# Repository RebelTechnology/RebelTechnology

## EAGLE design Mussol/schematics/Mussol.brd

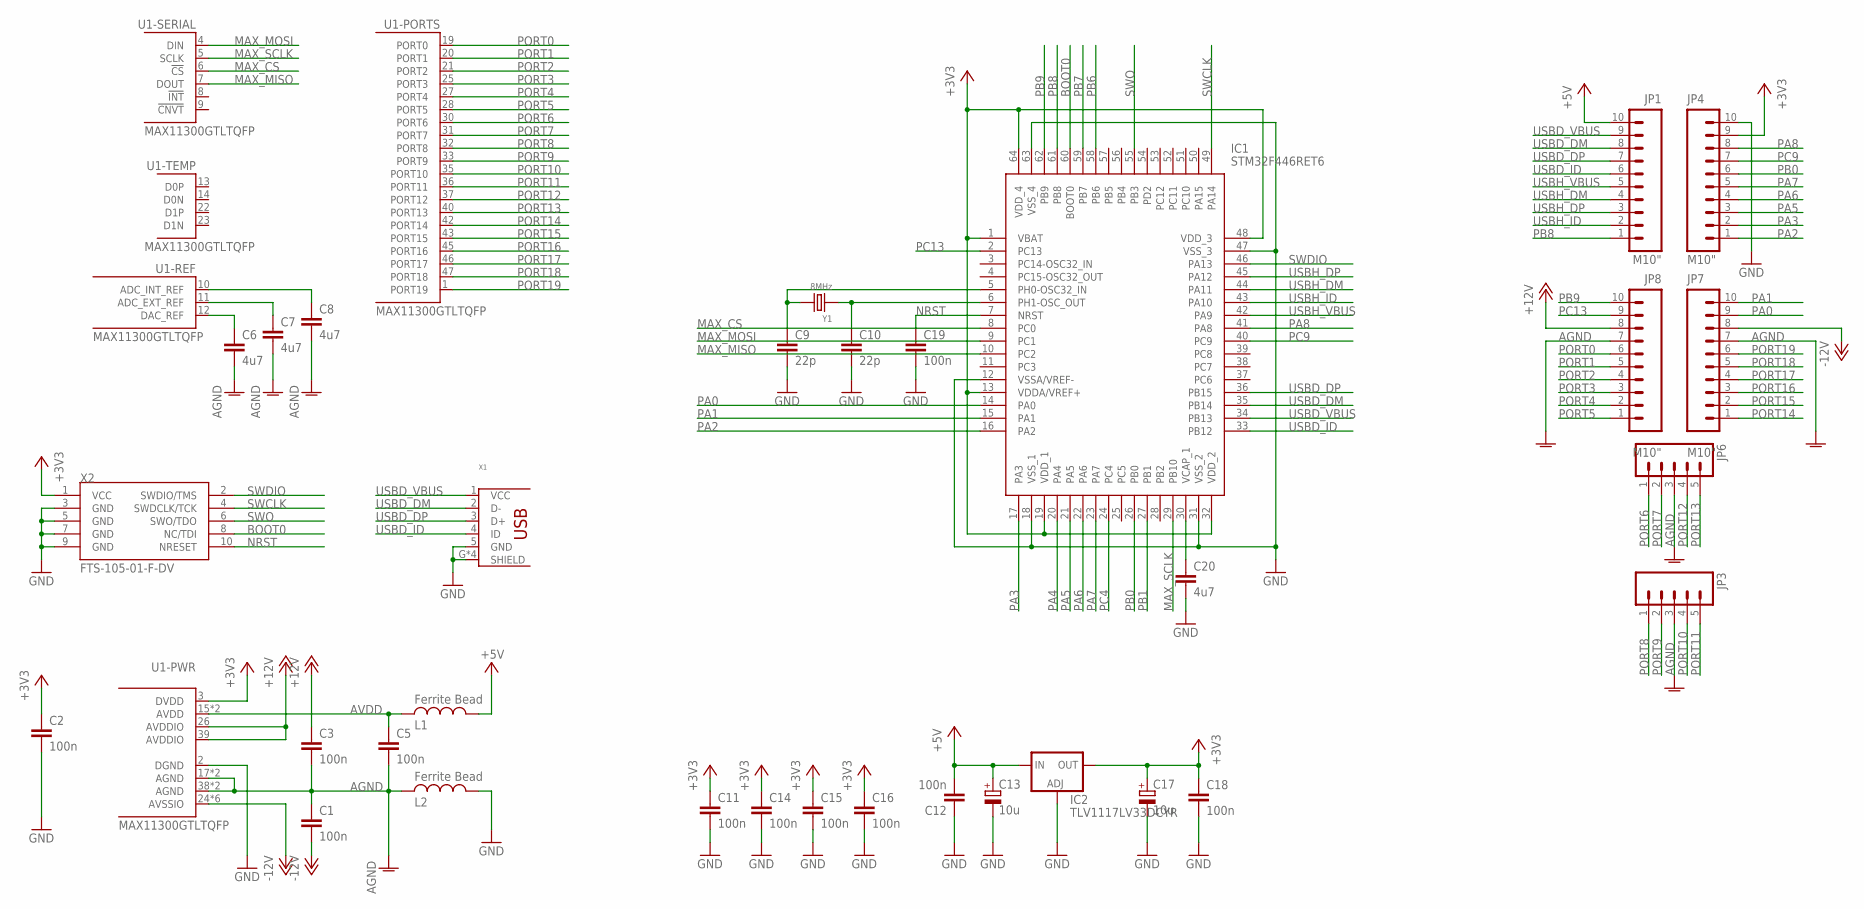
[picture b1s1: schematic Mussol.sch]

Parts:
C1, C2, C3, C5, C11, C12, C14, C15, C16, C18, C19: 100n; C0402
C6, C7, C8, C20: 4u7; C0603
C9, C10: 22p; C0402
C13, C17: 10u; UD-4X5,8_NICHICON
IC1: STM32F446RET6; QFP50P1200X1200X160-64N
IC2: TLV1117LV33DCYR; SOT223
JP1, JP4, JP7, JP8: M10"; 1X10
JP3, JP6: M05PTH; 1X05
L1, L2: Ferrite Bead; 0603
U1: MAX11300GTLTQFP; TQFP48
X1: USB_HRS_ZX62-B-5PA(11)MICRO.B; HRS_ZX62RD-AB-5P8
X2: FTS-105-01-F-DV; 2X5_1.27MM_SMD
Y1: 8MHz; X2-SMD-5.0X3.2X1.3MM

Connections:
+3V3: C2.1, C11.1, C14.1, C15.1, C16.1, C17.+, C18.1, IC1.1 (VBAT), IC1.13 (VDDA/VREF+), IC1.19 (VDD_1), IC1.32 (VDD_2), IC1.48 (VDD_3), IC1.64 (VDD_4), IC2.4 (OUT), JP4.9, U1.3 (DVDD), X2.1 (VCC)
+5V: C12.2, C13.+, IC2.3 (IN), JP1.10, L1.1
+12V: C3.1, JP8.8, U1.26 (AVDDIO), U1.39 (AVDDIO)
-12V: C1.2, JP7.8, U1.24 (AVSSIO), U1.29 (AVSSIO), U1.34 (AVSSIO), U1.41 (AVSSIO), U1.44 (AVSSIO), U1.48 (AVSSIO)
AGND: C1.1, C3.2, C5.2, C6.2, C7.2, C8.2, JP3.3, JP6.3, JP7.7, JP8.7, L2.2, U1.17 (AGND), U1.18 (AGND), U1.38 (AGND), U1.EP (AGND)
AVDD: C5.1, L1.2, U1.15 (AVDD), U1.16 (AVDD)
BOOT0: IC1.60 (BOOT0), X2.8 (NC/TDI)
GND: C2.2, C9.2, C10.2, C11.2, C12.1, C13.-, C14.2, C15.2, C16.2, C17.-, C18.2, C19.2, C20.2, IC1.12 (VSSA/VREF-), IC1.18 (VSS_1), IC1.31 (VSS_2), IC1.47 (VSS_3), IC1.63 (VSS_4), IC2.1 (ADJ), JP4.10, L2.1, U1.2 (DGND), X1.5 (GND), X1.G (SHIELD), X1.G2 (SHIELD), X1.G3 (SHIELD), X1.G4 (SHIELD), X2.3 (GND), X2.5 (GND), X2.7 (GND), X2.9 (GND)
MAX_CS: IC1.8 (PC0), U1.6 (!CS!)
MAX_MISO: IC1.10 (PC2), U1.7 (DOUT)
MAX_MOSI: IC1.9 (PC1), U1.4 (DIN)
MAX_SCLK: IC1.29 (PB10), U1.5 (SCLK)
unnamed: C8.1, U1.10 (ADC_INT_REF)
unnamed: C20.1, IC1.30 (VCAP_1)
unnamed: C7.1, U1.11 (ADC_EXT_REF)
unnamed: C6.1, U1.12 (DAC_REF)
unnamed: C10.1, IC1.6 (PH1-OSC_OUT), Y1.1
unnamed: C9.1, IC1.5 (PH0-OSC32_IN), Y1.2
NRST: C19.1, IC1.7 (NRST), X2.10 (NRESET)
PA0: IC1.14 (PA0), JP7.9
PA1: IC1.15 (PA1), JP7.10
PA2: IC1.16 (PA2), JP4.1
PA3: IC1.17 (PA3), JP4.2
PA4: IC1.20 (PA4)
PA5: IC1.21 (PA5), JP4.3
PA6: IC1.22 (PA6), JP4.4
PA7: IC1.23 (PA7), JP4.5
PA8: IC1.41 (PA8), JP4.8
PB0: IC1.26 (PB0), JP4.6
PB1: IC1.27 (PB1)
PB6: IC1.58 (PB6)
PB7: IC1.59 (PB7)
PB8: IC1.61 (PB8), JP1.1
PB9: IC1.62 (PB9), JP8.10
PC4: IC1.24 (PC4)
PC9: IC1.40 (PC9), JP4.7
PC13: IC1.2 (PC13), JP8.9
PORT0: JP8.6, U1.19 (PORT0)
PORT1: JP8.5, U1.20 (PORT1)
PORT2: JP8.4, U1.21 (PORT2)
PORT3: JP8.3, U1.25 (PORT3)
PORT4: JP8.2, U1.27 (PORT4)
PORT5: JP8.1, U1.28 (PORT5)
PORT6: JP6.1, U1.30 (PORT6)
PORT7: JP6.2, U1.31 (PORT7)
PORT8: JP3.1, U1.32 (PORT8)
PORT9: JP3.2, U1.33 (PORT9)
PORT10: JP3.4, U1.35 (PORT10)
PORT11: JP3.5, U1.36 (PORT11)
PORT12: JP6.4, U1.37 (PORT12)
PORT13: JP6.5, U1.40 (PORT13)
PORT14: JP7.1, U1.42 (PORT14)
PORT15: JP7.2, U1.43 (PORT15)
PORT16: JP7.3, U1.45 (PORT16)
PORT17: JP7.4, U1.46 (PORT17)
PORT18: JP7.5, U1.47 (PORT18)
PORT19: JP7.6, U1.1 (PORT19)
SWCLK: IC1.49 (PA14), X2.4 (SWDCLK/TCK)
SWDIO: IC1.46 (PA13), X2.2 (SWDIO/TMS)
SWO: IC1.55 (PB3), X2.6 (SWO/TDO)
USBD_DM: IC1.35 (PB14), JP1.8, X1.2 (D-)
USBD_DP: IC1.36 (PB15), JP1.7, X1.3 (D+)
USBD_ID: IC1.33 (PB12), JP1.6, X1.4 (ID)
USBD_VBUS: IC1.34 (PB13), JP1.9, X1.1 (VCC)
USBH_DM: IC1.44 (PA11), JP1.4
USBH_DP: IC1.45 (PA12), JP1.3
USBH_ID: IC1.43 (PA10), JP1.2
USBH_VBUS: IC1.42 (PA9), JP1.5

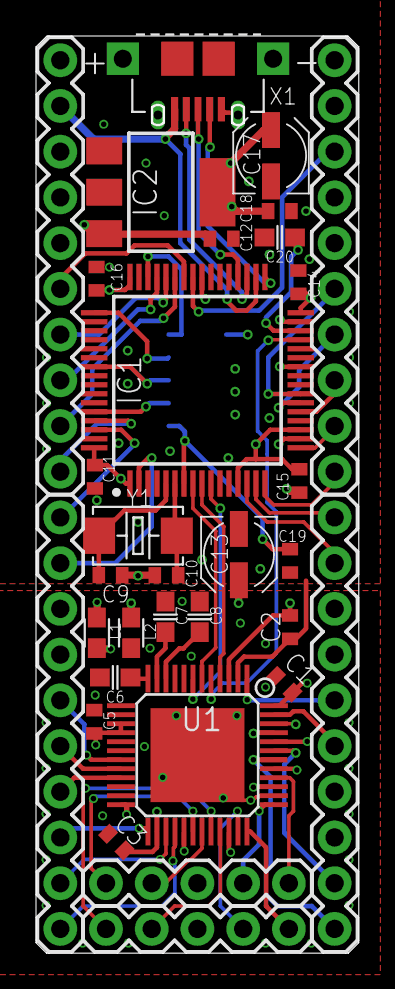
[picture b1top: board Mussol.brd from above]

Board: 4 copper layers, 17.9 x 51.0 mm, 33 parts (1 on the bottom side), 63 nets.

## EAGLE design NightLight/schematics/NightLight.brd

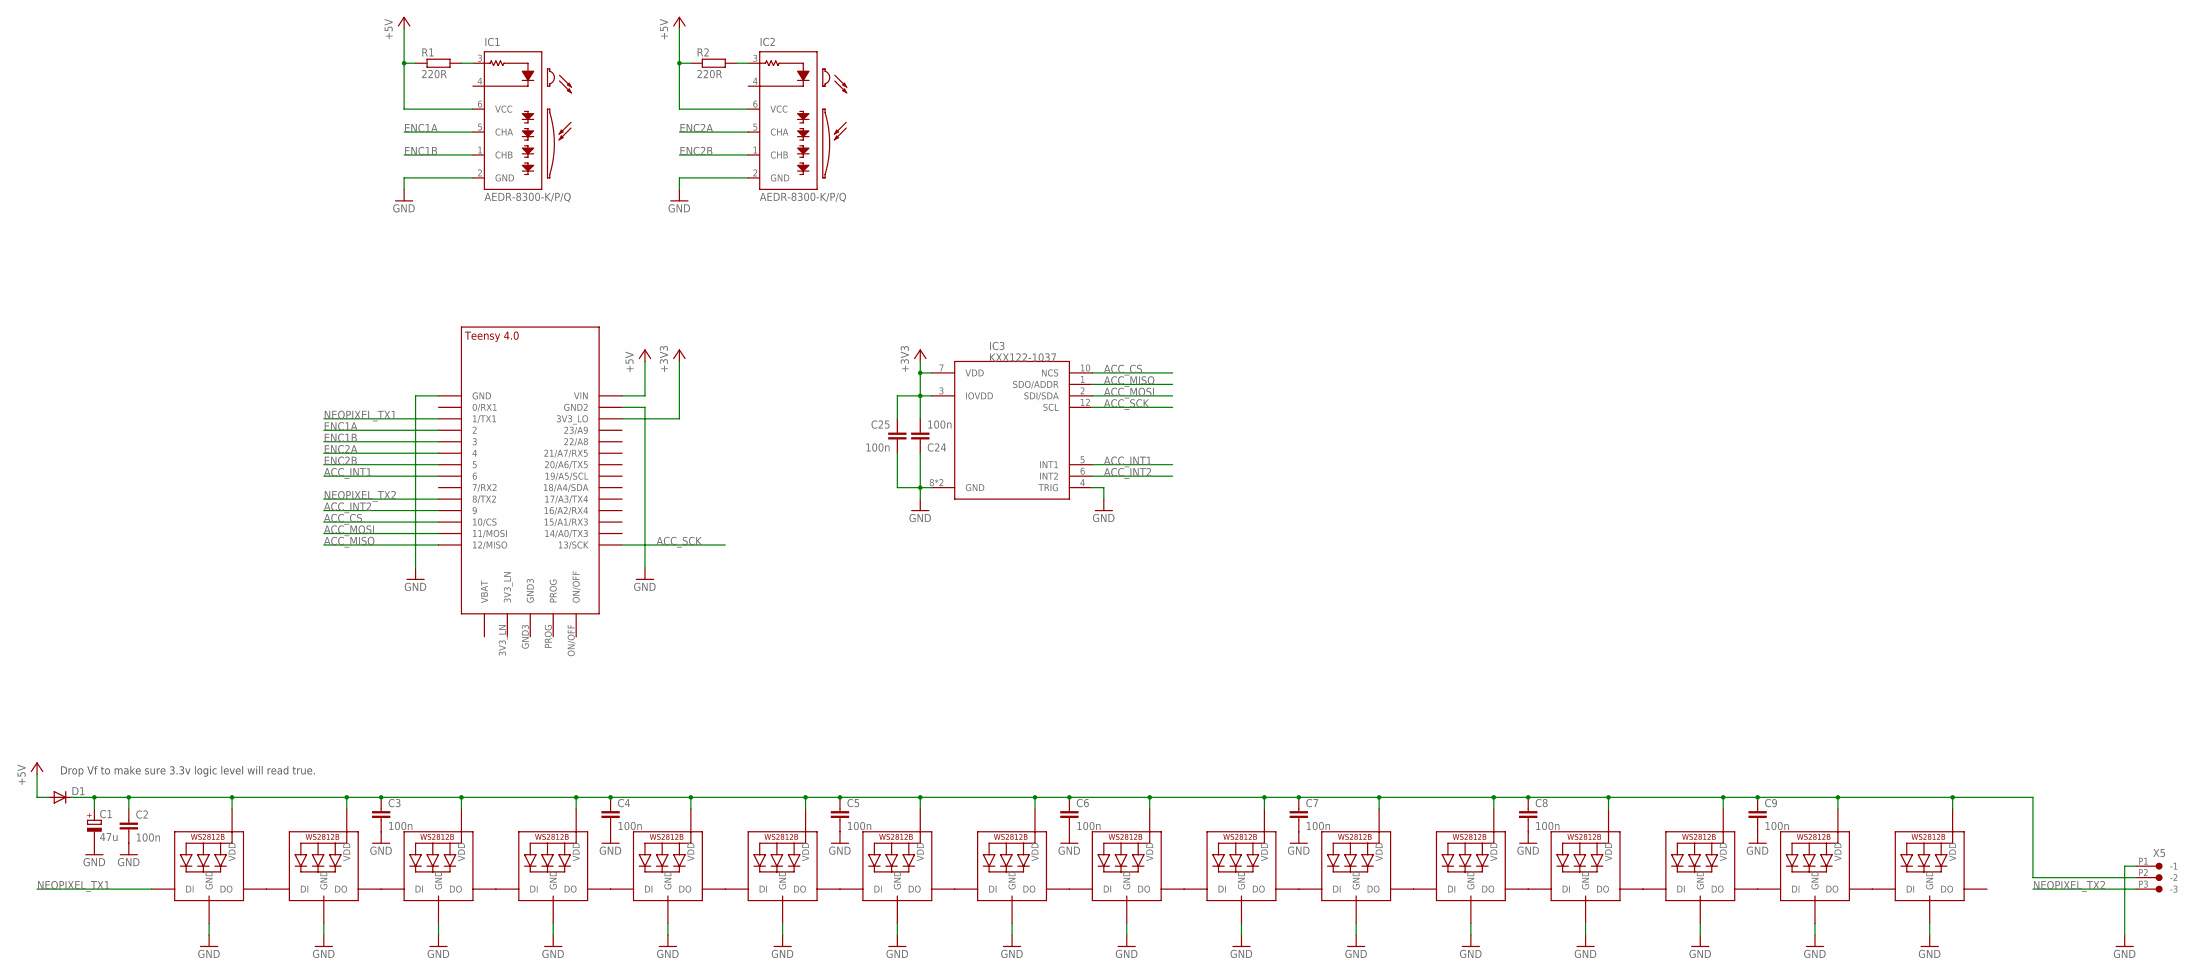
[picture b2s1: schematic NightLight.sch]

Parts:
C1: 47u; CPOL-5
C2, C3, C4, C5, C6, C7, C8, C9, C24, C25: 100n; C0603
D1: DIODE1N4001; DIODE-1N4001
IC1, IC2: AEDR-8300-K/P/Q; AEDR-8300
IC3: KXX122-1037; LGA16R50P4X4_200X200X100
LED1, LED2, LED3, LED4, LED5, LED6, LED7, LED8, LED9, LED10, LED11, LED12, LED13, LED14, LED15, LED16: WS2812B5050; WS2812B
R1, R2: 220R; 0603
U$1: TEENSY_4.0-BASIC
X5: CON-JST_PH_3W

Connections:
+3V3: C24.2, C25.1, IC3.3 (IOVDD), IC3.7 (VDD), U$1.3V3_LO
+5V: D1.A, IC1.6 (VCC), IC2.6 (VCC), R1.1, R2.1, U$1.VIN
ACC_CS: IC3.10 (NCS), U$1.10/CS
ACC_INT1: IC3.5 (INT1), U$1.6
ACC_INT2: IC3.6 (INT2), U$1.9/CS (9)
ACC_MISO: IC3.1 (SDO/ADDR), U$1.12/MISO
ACC_MOSI: IC3.2 (SDI/SDA), U$1.11/MOSI
ACC_SCK: IC3.12 (SCL), U$1.13/SCK
ENC1A: IC1.5 (CHA), U$1.2
ENC1B: IC1.1 (CHB), U$1.3/CANTX (3)
ENC2A: IC2.5 (CHA), U$1.4/CANRX (4)
ENC2B: IC2.1 (CHB), U$1.5
GND: C1.-, C2.2, C3.2, C4.2, C5.2, C6.2, C7.2, C8.2, C9.2, C24.1, C25.2, IC1.2 (GND), IC1.E1 (GND), IC1.E2 (GND), IC2.2 (GND), IC2.E1 (GND), IC2.E2 (GND), IC3.4 (TRIG), IC3.8 (GND), IC3.9 (GND), LED1.3-GND (GND), LED2.3-GND (GND), LED3.3-GND (GND), LED4.3-GND (GND), LED5.3-GND (GND), LED6.3-GND (GND), LED7.3-GND (GND), LED8.3-GND (GND), LED9.3-GND (GND), LED10.3-GND (GND), LED11.3-GND (GND), LED12.3-GND (GND), LED13.3-GND (GND), LED14.3-GND (GND), LED15.3-GND (GND), LED16.3-GND (GND), U$1.GND, U$1.GND2, X5.P1 (-1)
unnamed: IC1.3 (A), R1.2
unnamed: C1.+, C2.1, C3.1, C4.1, C5.1, C6.1, C7.1, C8.1, C9.1, D1.C, LED1.1-VDD (VDD), LED2.1-VDD (VDD), LED3.1-VDD (VDD), LED4.1-VDD (VDD), LED5.1-VDD (VDD), LED6.1-VDD (VDD), LED7.1-VDD (VDD), LED8.1-VDD (VDD), LED9.1-VDD (VDD), LED10.1-VDD (VDD), LED11.1-VDD (VDD), LED12.1-VDD (VDD), LED13.1-VDD (VDD), LED14.1-VDD (VDD), LED15.1-VDD (VDD), LED16.1-VDD (VDD), X5.P2 (-2)
unnamed: IC2.3 (A), R2.2
unnamed: LED1.2-DOUT (DO), LED2.4-DIN (DI)
unnamed: LED2.2-DOUT (DO), LED3.4-DIN (DI)
unnamed: LED3.2-DOUT (DO), LED4.4-DIN (DI)
unnamed: LED4.2-DOUT (DO), LED5.4-DIN (DI)
unnamed: LED5.2-DOUT (DO), LED6.4-DIN (DI)
unnamed: LED6.2-DOUT (DO), LED7.4-DIN (DI)
unnamed: LED7.2-DOUT (DO), LED8.4-DIN (DI)
unnamed: LED9.2-DOUT (DO), LED10.4-DIN (DI)
unnamed: LED10.2-DOUT (DO), LED11.4-DIN (DI)
unnamed: LED11.2-DOUT (DO), LED12.4-DIN (DI)
unnamed: LED12.2-DOUT (DO), LED13.4-DIN (DI)
unnamed: LED13.2-DOUT (DO), LED14.4-DIN (DI)
unnamed: LED14.2-DOUT (DO), LED15.4-DIN (DI)
unnamed: LED15.2-DOUT (DO), LED16.4-DIN (DI)
unnamed: LED8.2-DOUT (DO), LED9.4-DIN (DI)
NEOPIXEL_TX1: LED1.4-DIN (DI), U$1.1/TX (1/TX1)
NEOPIXEL_TX2: U$1.8 (8/TX2), X5.P3 (-3)

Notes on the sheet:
Drop Vf to make sure 3.3v logic level will read true.

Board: 2 copper layers, 35 parts (0 on the bottom side), 33 nets, no tracks yet.

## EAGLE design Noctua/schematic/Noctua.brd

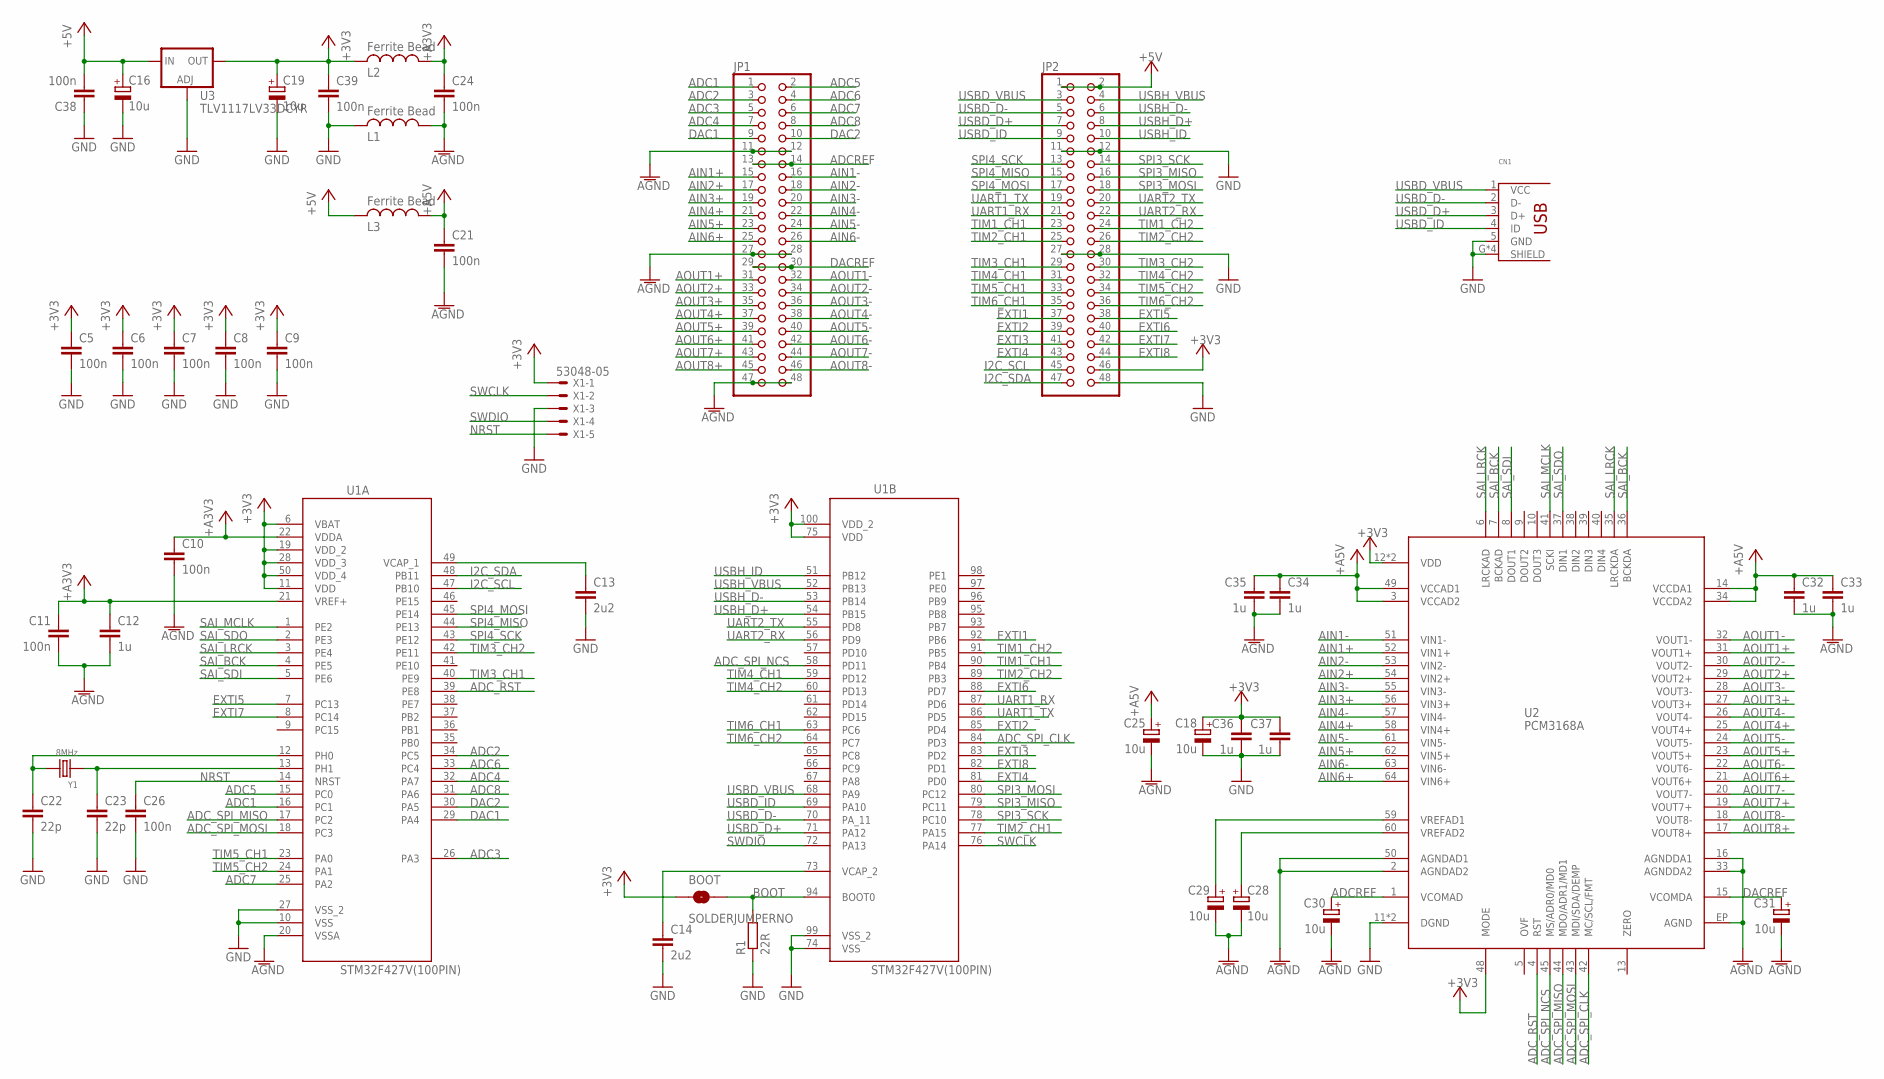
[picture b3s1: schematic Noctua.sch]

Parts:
BOOT: SOLDERJUMPERNO; SJ_2S-NO
C5, C6, C7, C8, C9, C10, C11, C21, C24, C26, C38, C39: 100n; C0603
C12, C32, C33, C34, C35, C36, C37: 1u; C0603
C13, C14: 2u2; C0603
C16, C18, C19, C25, C28, C29, C30, C31: 10u; UD-4X5,8_NICHICON
C22, C23: 22p; C0603
CN1: USB_HRS_ZX62-B-5PA(11)MICRO.B; HRS_ZX62RD-AB-5P8
JP1, JP2: PINHD-2X24; 2X24
L1, L2, L3: Ferrite Bead; 0603
R1: 22R; 0603@1
U1: STM32F427V(100PIN); QFP50P1600X1600X160-100N
U2: PCM3168A; PQFP64
U3: TLV1117LV33DCYR; SOT223
X1: 53048-05
Y1: 8MHz; X2-SMD-5.0X3.2X1.3MM

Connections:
+3V3: BOOT.1, C5.1, C6.1, C7.1, C8.1, C9.1, C18.+, C19.+, C36.1, C37.1, C39.1, JP2.46, L2.2, U1.6 (VBAT), U1.11 (VDD), U1.19 (VDD_2), U1.28 (VDD_3), U1.50 (VDD_4), U1.75 (VDD), U1.100 (VDD_2), U2.12 (VDD), U2.46 (VDD), U2.48 (MODE), U3.4 (OUT), X1.1
+5V: C16.+, C38.2, JP2.1, JP2.2, L3.2, U3.3 (IN)
+A3V3: C10.1, C11.1, C12.1, C24.1, L2.1, U1.21 (VREF+), U1.22 (VDDA)
+A5V: C21.1, C25.+, C32.1, C33.1, C34.1, C35.1, L3.1, U2.3 (VCCAD2), U2.14 (VCCDA1), U2.34 (VCCDA2), U2.49 (VCCAD1)
ADC1: JP1.1, U1.16 (PC1)
ADC2: JP1.3, U1.34 (PC5)
ADC3: JP1.5, U1.26 (PA3)
ADC4: JP1.7, U1.32 (PA7)
ADC5: JP1.2, U1.15 (PC0)
ADC6: JP1.4, U1.33 (PC4)
ADC7: JP1.6, U1.25 (PA2)
ADC8: JP1.8, U1.31 (PA6)
ADCREF: C30.+, JP1.13, JP1.14, U2.1 (VCOMAD)
ADC_RST: U1.39 (PE8), U2.4 (RST)
ADC_SPI_CLK: U1.84 (PD3), U2.42 (MC/SCL/FMT)
ADC_SPI_MISO: U1.17 (PC2), U2.44 (MDO/ADR1/MD1)
ADC_SPI_MOSI: U1.18 (PC3), U2.43 (MDI/SDA/DEMP)
ADC_SPI_NCS: U1.58 (PD11), U2.45 (MS/ADR0/MD0)
AGND: C10.2, C11.2, C12.2, C21.2, C24.2, C25.-, C28.-, C29.-, C30.-, C31.-, C32.2, C33.2, C34.2, C35.2, JP1.11, JP1.12, JP1.27, JP1.28, JP1.47, JP1.48, L1.1, U1.20 (VSSA), U2.2 (AGNDAD2), U2.16 (AGNDDA1), U2.33 (AGNDDA2), U2.50 (AGNDAD1), U2.EP (AGND)
AIN1+: JP1.15, U2.52 (VIN1+)
AIN1-: JP1.16, U2.51 (VIN1-)
AIN2+: JP1.17, U2.54 (VIN2+)
AIN2-: JP1.18, U2.53 (VIN2-)
AIN3+: JP1.19, U2.56 (VIN3+)
AIN3-: JP1.20, U2.55 (VIN3-)
AIN4+: JP1.21, U2.58 (VIN4+)
AIN4-: JP1.22, U2.57 (VIN4-)
AIN5+: JP1.23, U2.62 (VIN5+)
AIN5-: JP1.24, U2.61 (VIN5-)
AIN6+: JP1.25, U2.64 (VIN6+)
AIN6-: JP1.26, U2.63 (VIN6-)
AOUT1+: JP1.31, U2.31 (VOUT1+)
AOUT1-: JP1.32, U2.32 (VOUT1-)
AOUT2+: JP1.33, U2.29 (VOUT2+)
AOUT2-: JP1.34, U2.30 (VOUT2-)
AOUT3+: JP1.35, U2.27 (VOUT3+)
AOUT3-: JP1.36, U2.28 (VOUT3-)
AOUT4+: JP1.37, U2.25 (VOUT4+)
AOUT4-: JP1.38, U2.26 (VOUT4-)
AOUT5+: JP1.39, U2.23 (VOUT5+)
AOUT5-: JP1.40, U2.24 (VOUT5-)
AOUT6+: JP1.41, U2.21 (VOUT6+)
AOUT6-: JP1.42, U2.22 (VOUT6-)
AOUT7+: JP1.43, U2.19 (VOUT7+)
AOUT7-: JP1.44, U2.20 (VOUT7-)
AOUT8+: JP1.45, U2.17 (VOUT8+)
AOUT8-: JP1.46, U2.18 (VOUT8-)
BOOT: BOOT.2, R1.2, U1.94 (BOOT0)
DAC1: JP1.9, U1.29 (PA4)
DAC2: JP1.10, U1.30 (PA5)
DACREF: C31.+, JP1.29, JP1.30, U2.15 (VCOMDA)
EXTI1: JP2.37, U1.92 (PB6)
EXTI2: JP2.39, U1.85 (PD4)
EXTI3: JP2.41, U1.83 (PD2)
EXTI4: JP2.43, U1.81 (PD0)
EXTI5: JP2.38, U1.7 (PC13)
EXTI6: JP2.40, U1.88 (PD7)
EXTI7: JP2.42, U1.8 (PC14)
EXTI8: JP2.44, U1.82 (PD1)
GND: C5.2, C6.2, C7.2, C8.2, C9.2, C13.2, C14.2, C16.-, C18.-, C19.-, C22.2, C23.2, C26.2, C36.2, C37.2, C38.1, C39.2, CN1.5 (GND), CN1.G (SHIELD), CN1.G2 (SHIELD), CN1.G3 (SHIELD), CN1.G4 (SHIELD), JP2.11, JP2.12, JP2.27, JP2.28, JP2.48, L1.2, R1.1, U1.10 (VSS), U1.27 (VSS_2), U1.74 (VSS), U1.99 (VSS_2), U2.11 (DGND), U2.47 (DGND), U3.1 (ADJ), X1.3
I2C_SCL: JP2.45, U1.47 (PB10)
I2C_SDA: JP2.47, U1.48 (PB11)
unnamed: C28.+, U2.60 (VREFAD2)
unnamed: C13.1, U1.49 (VCAP_1)
unnamed: C23.1, U1.13 (PH1), Y1.1
unnamed: C22.1, U1.12 (PH0), Y1.2
unnamed: C14.1, U1.73 (VCAP_2)
NRST: C26.1, U1.14 (NRST), X1.5
SAI_BCK: U1.4 (PE5), U2.7 (BCKAD), U2.36 (BCKDA)
SAI_LRCK: U1.3 (PE4), U2.6 (LRCKAD), U2.35 (LRCKDA)
SAI_MCLK: U1.1 (PE2), U2.41 (SCKI)
SAI_SDI: U1.5 (PE6), U2.8 (DOUT1)
SAI_SDO: U1.2 (PE3), U2.37 (DIN1)
SPI3_MISO: JP2.16, U1.79 (PC11)
SPI3_MOSI: JP2.18, U1.80 (PC12)
SPI3_SCK: JP2.14, U1.78 (PC10)
SPI4_MISO: JP2.15, U1.44 (PE13)
SPI4_MOSI: JP2.17, U1.45 (PE14)
SPI4_SCK: JP2.13, U1.43 (PE12)
SWCLK: U1.76 (PA14), X1.2
SWDIO: U1.72 (PA13), X1.4
TIM1_CH1: JP2.23, U1.90 (PB4)
TIM1_CH2: JP2.24, U1.91 (PB5)
TIM2_CH1: JP2.25, U1.77 (PA15)
TIM2_CH2: JP2.26, U1.89 (PB3)
TIM3_CH1: JP2.29, U1.40 (PE9)
TIM3_CH2: JP2.30, U1.42 (PE11)
TIM4_CH1: JP2.31, U1.59 (PD12)
TIM4_CH2: JP2.32, U1.60 (PD13)
TIM5_CH1: JP2.33, U1.23 (PA0)
TIM5_CH2: JP2.34, U1.24 (PA1)
TIM6_CH1: JP2.35, U1.63 (PC6)
TIM6_CH2: JP2.36, U1.64 (PC7)
UART1_RX: JP2.21, U1.87 (PD6)
UART1_TX: JP2.19, U1.86 (PD5)
UART2_RX: JP2.22, U1.56 (PD9)
UART2_TX: JP2.20, U1.55 (PD8)
USBD_D+: CN1.3 (D+), JP2.7, U1.71 (PA12)
USBD_D-: CN1.2 (D-), JP2.5, U1.70 (PA_11)
USBD_ID: CN1.4 (ID), JP2.9, U1.69 (PA10)
USBD_VBUS: CN1.1 (VCC), JP2.3, U1.68 (PA9)
USBH_D+: JP2.8, U1.54 (PB15)
USBH_D-: JP2.6, U1.53 (PB14)
USBH_ID: JP2.10, U1.51 (PB12)
USBH_VBUS: JP2.4, U1.52 (PB13)
VREF_ADC: C29.+, U2.59 (VREFAD1)

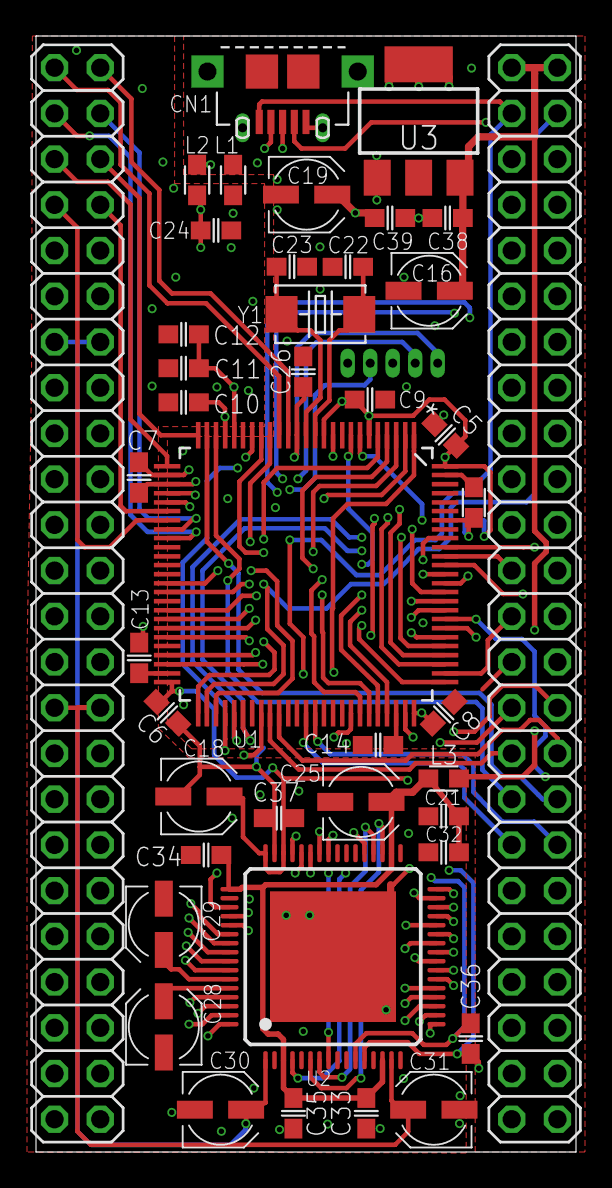
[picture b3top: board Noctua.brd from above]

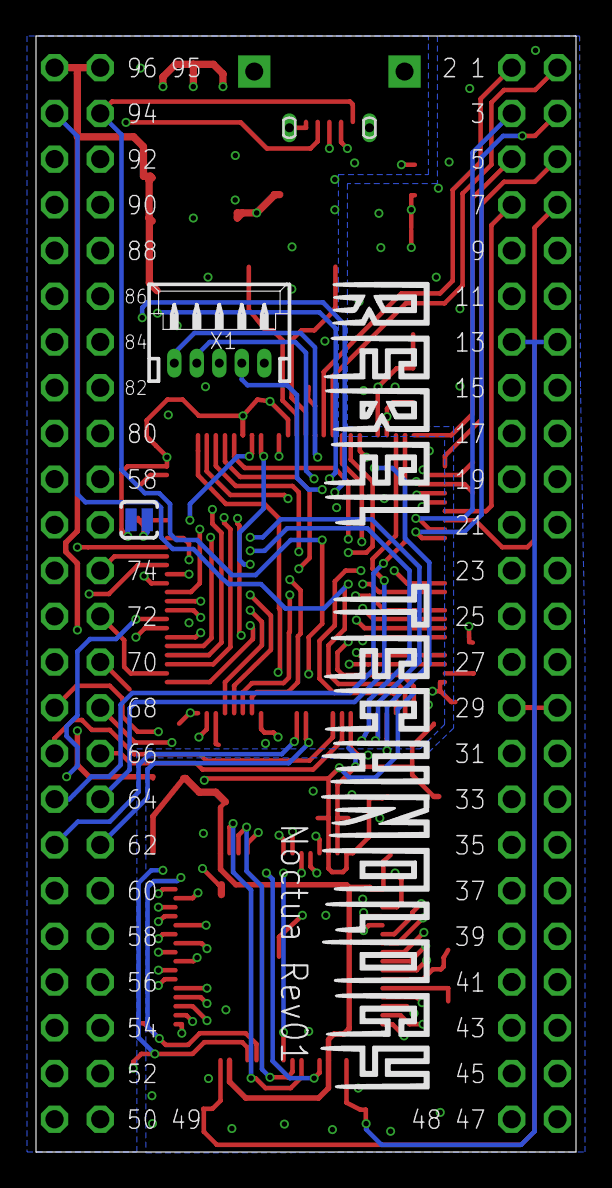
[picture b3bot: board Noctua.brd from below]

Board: 4 copper layers, 30.0 x 62.0 mm, 44 parts (2 on the bottom side), 106 nets.

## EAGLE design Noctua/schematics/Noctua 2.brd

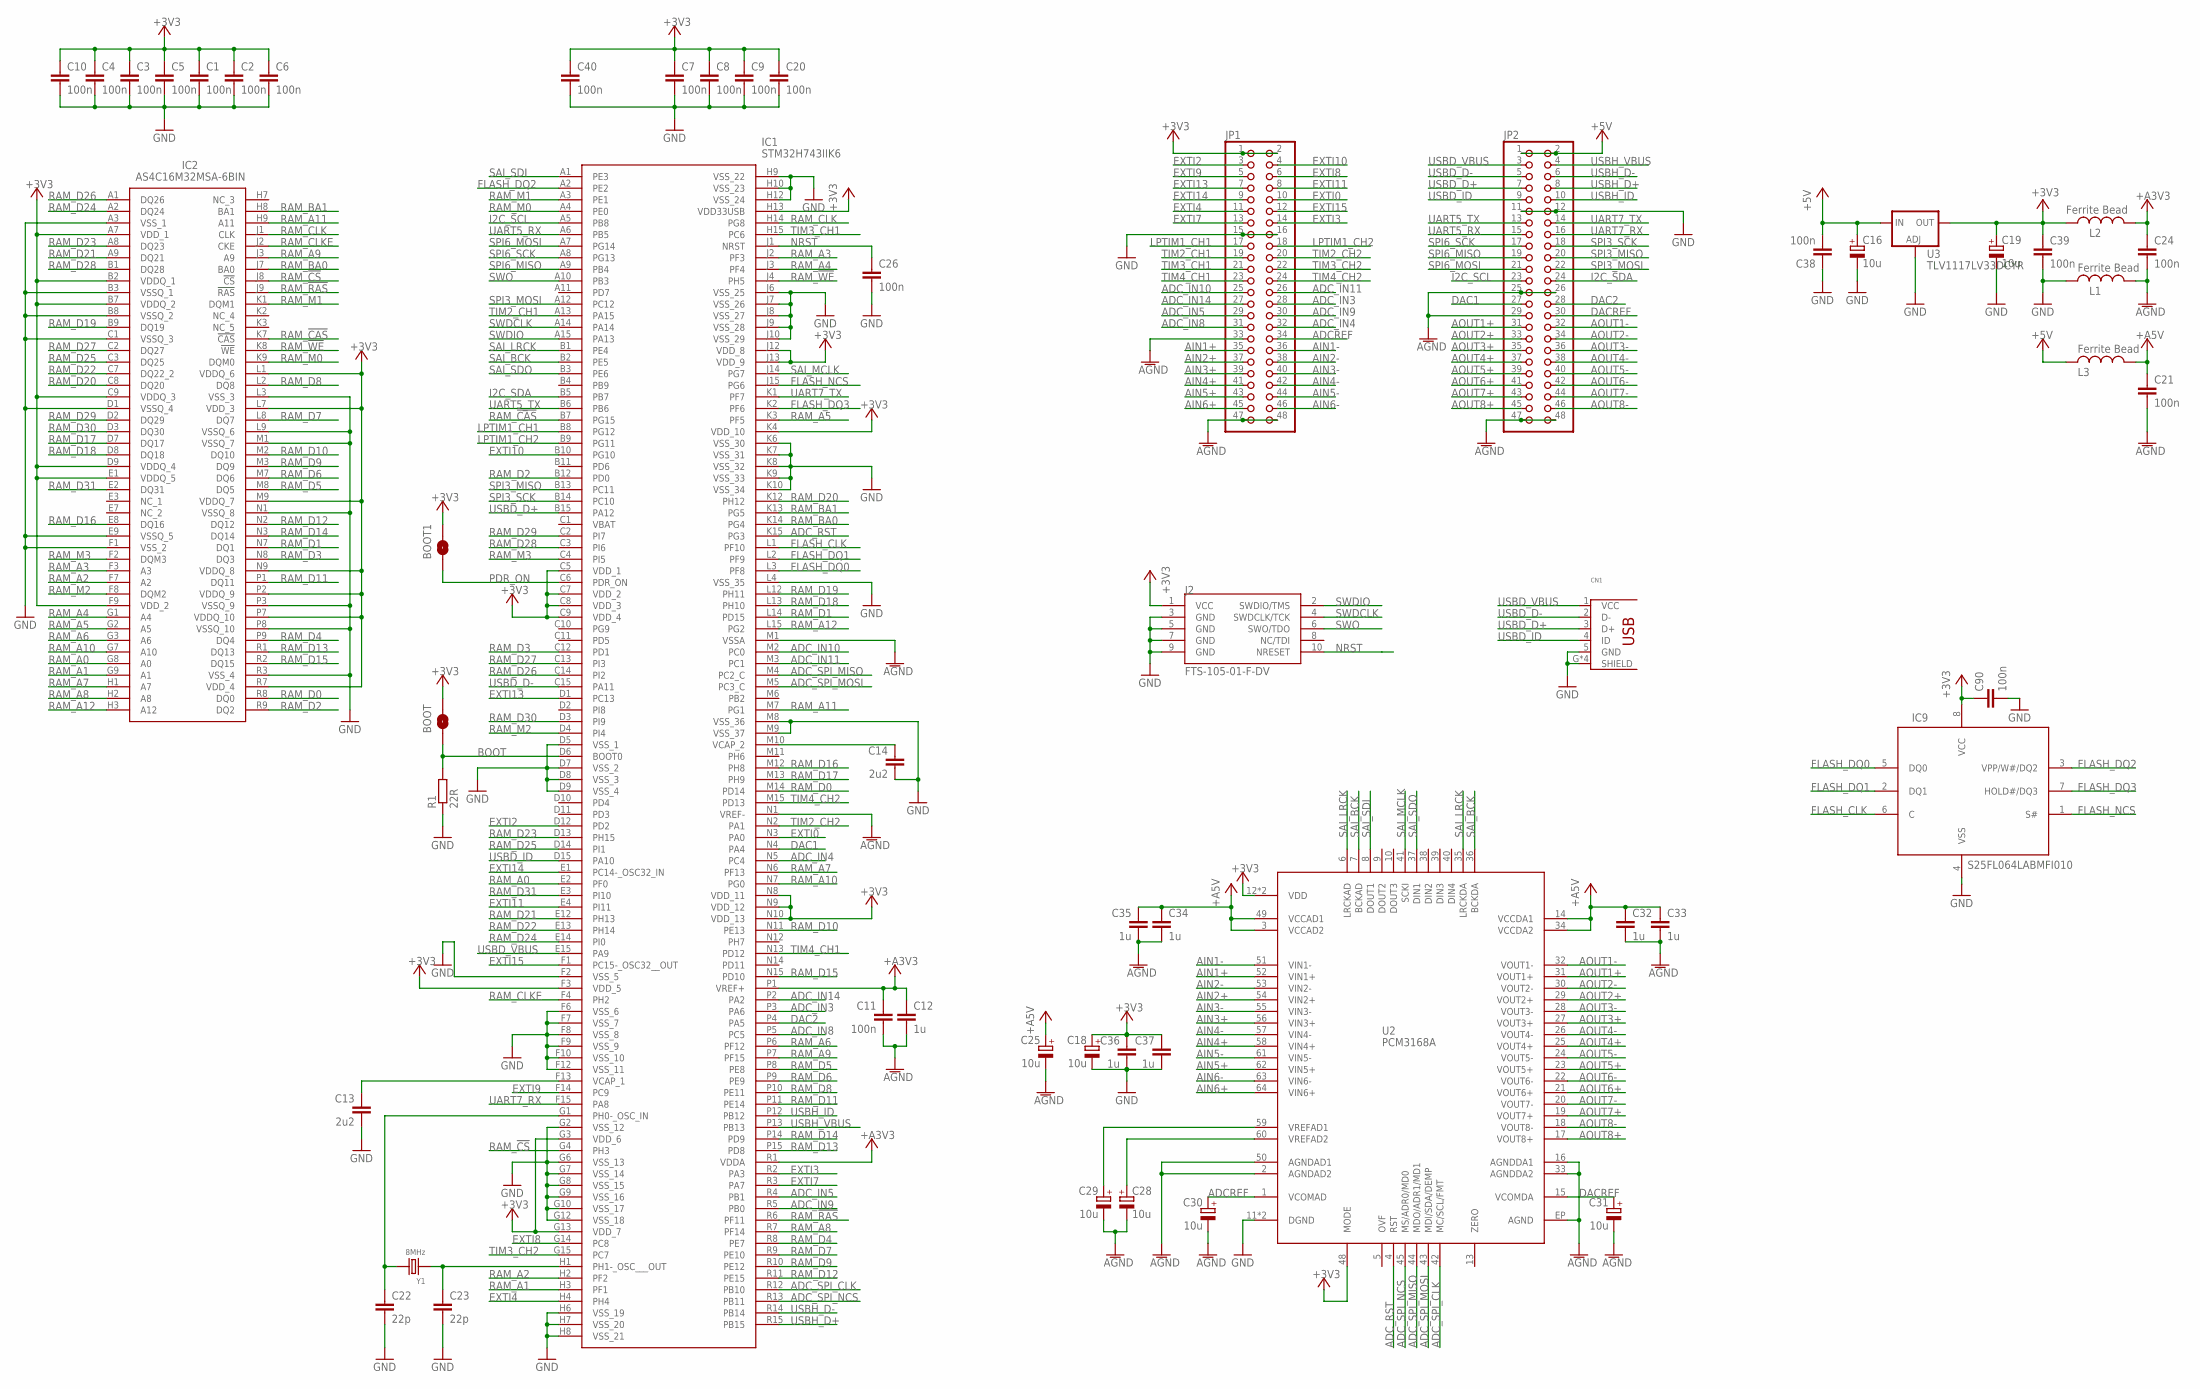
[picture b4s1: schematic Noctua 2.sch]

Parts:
BOOT, BOOT1: SOLDERJUMPERNO; SJ_2S-NO
C1, C2, C3, C4, C5, C6, C7, C8, C9, C10, C11, C20, C24, C26, C38, C39, C40, C90: 100n; C0402
C12: 1u; C0402
C13, C14: 2u2; C0402
C16, C18, C19, C25, C28, C29, C30, C31: 10u; UD-4X5,8_NICHICON
C21: 100n; C0603
C22, C23: 22p; C0402
C32, C33, C34, C35, C36, C37: 1u; C0603
CN1: USB_HRS_ZX62-B-5PA(11)MICRO.B; HRS_ZX62RD-AB-5P8
IC1: STM32H743IIK6; BGA201C65P15X15_1000X1000X60
IC2: AS4C16M32MSA-6BIN; BGA90C80P9X15_800X1300X100
IC9: S25FL064LABMFI010; SO8W
J2: FTS-105-01-F-DV; 2X5_1.27MM_SMD
JP1, JP2: PINHD-2X24; 2X24
L1, L2, L3: Ferrite Bead; 0603
R1: 22R; 0603
U2: PCM3168A; PQFP64
U3: TLV1117LV33DCYR; SOT223
Y1: 8MHz; X2-SMD-5.0X3.2X1.3MM

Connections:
+3V3: BOOT.1, BOOT1.1, C1.1, C2.1, C3.1, C4.1, C5.1, C6.1, C7.1, C8.1, C9.1, C10.1, C18.+, C19.+, C20.1, C36.1, C37.1, C39.1, C40.1, C90.1, IC1.C5 (VDD_1), IC1.C7 (VDD_2), IC1.C8 (VDD_3), IC1.C9 (VDD_4), IC1.F3 (VDD_5), IC1.G3 (VDD_6), IC1.G13 (VDD_7), IC1.H13 (VDD33USB), IC1.J12 (VDD_8), IC1.J13 (VDD_9), IC1.K4 (VDD_10), IC1.N8 (VDD_11), IC1.N9 (VDD_12), IC1.N10 (VDD_13), IC2.A7 (VDD_1), IC2.B2 (VDDQ_1), IC2.B7 (VDDQ_2), IC2.C9 (VDDQ_3), IC2.D9 (VDDQ_4), IC2.E1 (VDDQ_5), IC2.F9 (VDD_2), IC2.L1 (VDDQ_6), IC2.L7 (VDD_3), IC2.M9 (VDDQ_7), IC2.N9 (VDDQ_8), IC2.P2 (VDDQ_9), IC2.P7 (VDDQ_10), IC2.R7 (VDD_4), IC9.8 (VCC), J2.1 (VCC), JP1.1, JP1.2, L2.2, U2.12 (VDD), U2.46 (VDD), U2.48 (MODE), U3.4 (OUT)
+5V: C16.+, C38.2, JP2.1, JP2.2, L3.2, U3.3 (IN)
+A3V3: C11.1, C12.1, C24.1, IC1.P1 (VREF+), IC1.R1 (VDDA), L2.1
+A5V: C21.1, C25.+, C32.1, C33.1, C34.1, C35.1, L3.1, U2.3 (VCCAD2), U2.14 (VCCDA1), U2.34 (VCCDA2), U2.49 (VCCAD1)
ADCREF: C30.+, JP1.34, U2.1 (VCOMAD)
ADC_IN3: IC1.P3 (PA6), JP1.28
ADC_IN4: IC1.N5 (PC4), JP1.32
ADC_IN5: IC1.R4 (PB1), JP1.29
ADC_IN8: IC1.P5 (PC5), JP1.31
ADC_IN9: IC1.R5 (PB0), JP1.30
ADC_IN10: IC1.M2 (PC0), JP1.25
ADC_IN11: IC1.M3 (PC1), JP1.26
ADC_IN14: IC1.P2 (PA2), JP1.27
ADC_RST: IC1.K15 (PG3), U2.4 (RST)
ADC_SPI_CLK: IC1.R12 (PB10), U2.42 (MC/SCL/FMT)
ADC_SPI_MISO: IC1.M4 (PC2_C), U2.44 (MDO/ADR1/MD1)
ADC_SPI_MOSI: IC1.M5 (PC3_C), U2.43 (MDI/SDA/DEMP)
ADC_SPI_NCS: IC1.R13 (PB11), U2.45 (MS/ADR0/MD0)
AGND: C11.2, C12.2, C21.2, C24.2, C25.-, C28.-, C29.-, C30.-, C31.-, C32.2, C33.2, C34.2, C35.2, IC1.M1 (VSSA), IC1.N1 (VREF-), JP1.33, JP1.47, JP1.48, JP2.25, JP2.26, JP2.29, JP2.47, JP2.48, L1.1, U2.2 (AGNDAD2), U2.16 (AGNDDA1), U2.33 (AGNDDA2), U2.50 (AGNDAD1), U2.EP (AGND)
AIN1+: JP1.35, U2.52 (VIN1+)
AIN1-: JP1.36, U2.51 (VIN1-)
AIN2+: JP1.37, U2.54 (VIN2+)
AIN2-: JP1.38, U2.53 (VIN2-)
AIN3+: JP1.39, U2.56 (VIN3+)
AIN3-: JP1.40, U2.55 (VIN3-)
AIN4+: JP1.41, U2.58 (VIN4+)
AIN4-: JP1.42, U2.57 (VIN4-)
AIN5+: JP1.43, U2.62 (VIN5+)
AIN5-: JP1.44, U2.61 (VIN5-)
AIN6+: JP1.45, U2.64 (VIN6+)
AIN6-: JP1.46, U2.63 (VIN6-)
AOUT1+: JP2.31, U2.31 (VOUT1+)
AOUT1-: JP2.32, U2.32 (VOUT1-)
AOUT2+: JP2.33, U2.29 (VOUT2+)
AOUT2-: JP2.34, U2.30 (VOUT2-)
AOUT3+: JP2.35, U2.27 (VOUT3+)
AOUT3-: JP2.36, U2.28 (VOUT3-)
AOUT4+: JP2.37, U2.25 (VOUT4+)
AOUT4-: JP2.38, U2.26 (VOUT4-)
AOUT5+: JP2.39, U2.23 (VOUT5+)
AOUT5-: JP2.40, U2.24 (VOUT5-)
AOUT6+: JP2.41, U2.21 (VOUT6+)
AOUT6-: JP2.42, U2.22 (VOUT6-)
AOUT7+: JP2.43, U2.19 (VOUT7+)
AOUT7-: JP2.44, U2.20 (VOUT7-)
AOUT8+: JP2.45, U2.17 (VOUT8+)
AOUT8-: JP2.46, U2.18 (VOUT8-)
BOOT: BOOT.2, IC1.D6 (BOOT0), R1.2
DAC1: IC1.N4 (PA4), JP2.27
DAC2: IC1.P4 (PA5), JP2.28
DACREF: C31.+, JP2.30, U2.15 (VCOMDA)
EXTI0: IC1.N3 (PA0), JP1.10
EXTI2: IC1.D12 (PD2), JP1.3
EXTI3: IC1.R2 (PA3), JP1.14
EXTI4: IC1.H4, JP1.11
EXTI7: IC1.R3 (PA7), JP1.13
EXTI8: IC1.G14 (PC8), JP1.6
EXTI9: IC1.F14 (PC9), JP1.5
EXTI10: IC1.B10 (PG10), JP1.4
EXTI11: IC1.E4 (PI11), JP1.8
EXTI13: IC1.D1 (PC13), JP1.7
EXTI14: IC1.E1 (PC14-_OSC32_IN), JP1.9
EXTI15: IC1.F1 (PC15-_OSC32__OUT), JP1.12
FLASH_CLK: IC1.L1 (PF10), IC9.6 (C)
FLASH_DQ0: IC1.L3 (PF8), IC9.5 (DQ0)
FLASH_DQ1: IC1.L2 (PF9), IC9.2 (DQ1)
FLASH_DQ2: IC1.A2 (PE2), IC9.3 (VPP/W#/DQ2)
FLASH_DQ3: IC1.K2 (PF6), IC9.7 (HOLD#/DQ3)
FLASH_NCS: IC1.J15 (PG6), IC9.1 (S#)
GND: C1.2, C2.2, C3.2, C4.2, C5.2, C6.2, C7.2, C8.2, C9.2, C10.2, C13.2, C14.2, C16.-, C18.-, C19.-, C20.2, C22.2, C23.2, C26.2, C36.2, C37.2, C38.1, C39.2, C40.2, C90.2, CN1.5 (GND), CN1.G (SHIELD), CN1.G2 (SHIELD), CN1.G3 (SHIELD), CN1.G4 (SHIELD), IC1.D5 (VSS_1), IC1.D7 (VSS_2), IC1.D8 (VSS_3), IC1.D9 (VSS_4), IC1.F2 (VSS_5), IC1.F6 (VSS_6), IC1.F7 (VSS_7), IC1.F8 (VSS_8), IC1.F9 (VSS_9), IC1.F10 (VSS_10), IC1.F12 (VSS_11), IC1.G2 (VSS_12), IC1.G6 (VSS_13), IC1.G7 (VSS_14), IC1.G8 (VSS_15), IC1.G9 (VSS_16), IC1.G10 (VSS_17), IC1.G12 (VSS_18), IC1.H6 (VSS_19), IC1.H7 (VSS_20), IC1.H8 (VSS_21), IC1.H9 (VSS_22), IC1.H10 (VSS_23), IC1.H12 (VSS_24), IC1.J6 (VSS_25), IC1.J7 (VSS_26), IC1.J8 (VSS_27), IC1.J9 (VSS_28), IC1.J10 (VSS_29), IC1.K6 (VSS_30), IC1.K7 (VSS_31), IC1.K8 (VSS_32), IC1.K9 (VSS_33), IC1.K10 (VSS_34), IC1.L4 (VSS_35), IC1.M8 (VSS_36), IC1.M9 (VSS_37), IC2.A3 (VSS_1), IC2.B3 (VSSQ_1), IC2.B8 (VSSQ_2), IC2.C1 (VSSQ_3), IC2.D1 (VSSQ_4), IC2.E9 (VSSQ_5), IC2.F1 (VSS_2), IC2.L3 (VSS_3), IC2.L9 (VSSQ_6), IC2.M1 (VSSQ_7), IC2.N1 (VSSQ_8), IC2.P3 (VSSQ_9), IC2.P8 (VSSQ_10), IC2.R3 (VSS_4), IC9.4 (VSS), J2.3 (GND), J2.5 (GND), J2.7 (GND), J2.9 (GND), JP1.15, JP1.16, JP2.11, JP2.12, L1.2, R1.1, U2.11 (DGND), U2.47 (DGND), U3.1 (ADJ)
I2C_SCL: IC1.A5 (PB8), JP2.23
I2C_SDA: IC1.B5 (PB7), JP2.24
LPTIM1_CH1: IC1.B8 (PG12), JP1.17
LPTIM1_CH2: IC1.B9 (PG11), JP1.18
unnamed: C14.1, IC1.M10 (VCAP_2)
unnamed: C28.+, U2.60 (VREFAD2)
unnamed: C13.1, IC1.F13 (VCAP_1)
unnamed: C23.1, IC1.H1 (PH1-_OSC___OUT), Y1.1
unnamed: C22.1, IC1.G1 (PH0-_OSC_IN), Y1.2
NRST: C26.1, IC1.J1 (NRST), J2.10 (NRESET)
PDR_ON: BOOT1.2, IC1.C6 (PDR_ON)
RAM_!CAS: IC1.B7 (PG15), IC2.K7 (!CAS)
RAM_!CS: IC1.G4 (PH3), IC2.J8 (!CS)
RAM_!RAS: IC1.R6 (PF11), IC2.J9 (!RAS)
RAM_!WE: IC1.J4 (PH5), IC2.K8 (!WE)
RAM_A0: IC1.E2 (PF0), IC2.G8 (A0)
RAM_A1: IC1.H3 (PF1), IC2.G9 (A1)
RAM_A2: IC1.H2 (PF2), IC2.F7 (A2)
RAM_A3: IC1.J2 (PF3), IC2.F3 (A3)
RAM_A4: IC1.J3 (PF4), IC2.G1 (A4)
RAM_A5: IC1.K3 (PF5), IC2.G2 (A5)
RAM_A6: IC1.P6 (PF12), IC2.G3 (A6)
RAM_A7: IC1.N6 (PF13), IC2.H1 (A7)
RAM_A8: IC1.R7 (PF14), IC2.H2 (A8)
RAM_A9: IC1.P7 (PF15), IC2.J3 (A9)
RAM_A10: IC1.N7 (PG0), IC2.G7 (A10)
RAM_A11: IC1.M7 (PG1), IC2.H9 (A11)
RAM_A12: IC1.L15 (PG2), IC2.H3 (A12)
RAM_BA0: IC1.K14 (PG4), IC2.J7 (BA0)
RAM_BA1: IC1.K13 (PG5), IC2.H8 (BA1)
RAM_CLK: IC1.H14 (PG8), IC2.J1 (CLK)
RAM_CLKE: IC1.F4 (PH2), IC2.J2 (CKE)
RAM_D0: IC1.M14 (PD14), IC2.R8 (DQ0)
RAM_D1: IC1.L14 (PD15), IC2.N7 (DQ1)
RAM_D2: IC1.B12 (PD0), IC2.R9 (DQ2)
RAM_D3: IC1.C12 (PD1), IC2.N8 (DQ3)
RAM_D4: IC1.R8 (PE7), IC2.P9 (DQ4)
RAM_D5: IC1.P8 (PE8), IC2.M8 (DQ5)
RAM_D6: IC1.P9 (PE9), IC2.M7 (DQ6)
RAM_D7: IC1.R9 (PE10), IC2.L8 (DQ7)
RAM_D8: IC1.P10 (PE11), IC2.L2 (DQ8)
RAM_D9: IC1.R10 (PE12), IC2.M3 (DQ9)
RAM_D10: IC1.N11 (PE13), IC2.M2 (DQ10)
RAM_D11: IC1.P11 (PE14), IC2.P1 (DQ11)
RAM_D12: IC1.R11 (PE15), IC2.N2 (DQ12)
RAM_D13: IC1.P15 (PD8), IC2.R1 (DQ13)
RAM_D14: IC1.P14 (PD9), IC2.N3 (DQ14)
RAM_D15: IC1.N15 (PD10), IC2.R2 (DQ15)
RAM_D16: IC1.M12 (PH8), IC2.E8 (DQ16)
RAM_D17: IC1.M13 (PH9), IC2.D7 (DQ17)
RAM_D18: IC1.L13 (PH10), IC2.D8 (DQ18)
RAM_D19: IC1.L12 (PH11), IC2.B9 (DQ19)
RAM_D20: IC1.K12 (PH12), IC2.C8 (DQ20)
RAM_D21: IC1.E12 (PH13), IC2.A9 (DQ21)
RAM_D22: IC1.E13 (PH14), IC2.C7 (DQ22_2)
RAM_D23: IC1.D13 (PH15), IC2.A8 (DQ23)
RAM_D24: IC1.E14 (PI0), IC2.A2 (DQ24)
RAM_D25: IC1.D14 (PI1), IC2.C3 (DQ25)
RAM_D26: IC1.C14 (PI2), IC2.A1 (DQ26)
RAM_D27: IC1.C13 (PI3), IC2.C2 (DQ27)
RAM_D28: IC1.C3 (PI6), IC2.B1 (DQ28)
RAM_D29: IC1.C2 (PI7), IC2.D2 (DQ29)
RAM_D30: IC1.D3 (PI9), IC2.D3 (DQ30)
RAM_D31: IC1.E3 (PI10), IC2.E2 (DQ31)
RAM_M0: IC1.A4 (PE0), IC2.K9 (DQM0)
RAM_M1: IC1.A3 (PE1), IC2.K1 (DQM1)
RAM_M2: IC1.D4 (PI4), IC2.F8 (DQM2)
RAM_M3: IC1.C4 (PI5), IC2.F2 (DQM3)
SAI_BCK: IC1.B2 (PE5), U2.7 (BCKAD), U2.36 (BCKDA)
SAI_LRCK: IC1.B1 (PE4), U2.6 (LRCKAD), U2.35 (LRCKDA)
SAI_MCLK: IC1.J14 (PG7), U2.41 (SCKI)
SAI_SDI: IC1.A1 (PE3), U2.8 (DOUT1)
SAI_SDO: IC1.B3 (PE6), U2.37 (DIN1)
SPI3_MISO: IC1.B13 (PC11), JP2.20
SPI3_MOSI: IC1.A12 (PC12), JP2.22
SPI3_SCK: IC1.B14 (PC10), JP2.18
SPI6_MISO: IC1.A9 (PB4), JP2.19
SPI6_MOSI: IC1.A7 (PG14), JP2.21
SPI6_SCK: IC1.A8 (PG13), JP2.17
SWDCLK: IC1.A14, J2.4 (SWDCLK/TCK)
SWDIO: IC1.A15 (PA13), J2.2 (SWDIO/TMS)
SWO: IC1.A10 (PB3), J2.6 (SWO/TDO)
TIM2_CH1: IC1.A13 (PA15), JP1.19
TIM2_CH2: IC1.N2 (PA1), JP1.20
TIM3_CH1: IC1.H15 (PC6), JP1.21
TIM3_CH2: IC1.G15 (PC7), JP1.22
TIM4_CH1: IC1.N13 (PD12), JP1.23
TIM4_CH2: IC1.M15 (PD13), JP1.24
UART5_RX: IC1.A6 (PB5), JP2.15
UART5_TX: IC1.B6, JP2.13
UART7_RX: IC1.F15 (PA8), JP2.16
UART7_TX: IC1.K1 (PF7), JP2.14
USBD_D+: CN1.3 (D+), IC1.B15 (PA12), JP2.7
USBD_D-: CN1.2 (D-), IC1.C15 (PA11), JP2.5
USBD_ID: CN1.4 (ID), IC1.D15 (PA10), JP2.9
USBD_VBUS: CN1.1 (VCC), IC1.E15 (PA9), JP2.3
USBH_D+: IC1.R15 (PB15), JP2.8
USBH_D-: IC1.R14 (PB14), JP2.6
USBH_ID: IC1.P12 (PB12), JP2.10
USBH_VBUS: IC1.P13 (PB13), JP2.4
VREF_ADC: C29.+, U2.59 (VREFAD1)

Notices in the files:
parts and their libraries:
SparkFun: Licensing: CC v3.0 Share-Alike You are welcome to use this library for commercial purposes.
